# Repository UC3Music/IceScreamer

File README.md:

# IceScreamer
UC3Music's version of the well known green guitar pedal: Ibanez's Tube Screamer.

[Este mismo artículo en español](https://github.com/UC3Music/IceScreamer/blob/master/LEEME.md)

This project has a very similar electronics to Ibanez TS-808 TubeScreamer. Moreover this board let you choose among several modifications of the original design, and implement it easily. The most important modification is the ability to build a true bypass or buffered bypass pedal. Also there will be plenty of room for the most usual mods out there:

- Easier to provide "more gain"
- Easy to replace Op-Amp
- Easy to swap diodes (different distortion sounds)
- Easy to swap between flavors TS5, TS10 and TS808

## Choose from true bypass or pseudo true bypass.
From a manufacture perspective, true bypass isn't a convenient design, since it requires a big and expensive three pole, dual trow switch. And because it's bulkiness and complexity it needs to be soldered by hand. Buffered bypass is the way several manufacturers (Boss, Ibanez) reduced fabrication cost. However you need to solder 30 more components to get buffered bypass working, this circuit is more interesting in very automated manufacturing lines.

Among other benefits, true bypass means that, when your pedal is off, signal passes completely unaltered trough the pedal, as a wire tying together the input and output jack. Your tone will be perfect, however this bypass method has two disadvantages:

- A loud "click" sound can be made at the switch and then amplified by your guitar amp.
- If you are using long cable runs (i.e. 6m from guitar to pedalboard, then 6m from pedalboard to amp) you will have treble loss because guitar's high impedance output signal is affected a lot by cable capacitance.

Pseudo true bypass (buffered bypass) means that, when pedal is off, signal passes trough one or more buffers. A buffer is a kind of amplifier with gain of 1. Neither amplifies or attenuates signal. Buffers are designed to not alter the sound, but according to this [YouTube Video](https://www.youtube.com/watch?v=-oxBlWmeGE0), using more than five buffered pedals, bypass can trim down some bass frequencies and a little high frequencies. The benefits from buffered bypass are:

- No "click" silent switching.
- After the buffered pedal no matter how many cable meters you put, you no longer have treble loss. Pedal's output has low impedance, so cable capacitance reduce highs less.

TL;DR: using a lot of buffered bypass pedals is not good because you can end with a high-passed guitar sound. Using only true bypass pedals is not good if you handle long cable runs. Putting some buffered bypass pedal provide the best of the two worlds solution.

If you choose to build your IceScreamer with true bypass, short only "Short for TruBy" jumper located under "MILK" connector. If you choose to build your IceScreamer with pseudo true bypass, short only the two "Short both for Pseudo" jumpers, located in between input and output jacks.
Do it with a little of solder.

## Let's begin soldering
Components appears in the order it is meant to be soldered, from little to bigger size. If you need advice on how to solder, check this videos.
- [Tutorial SMT4Dummies by David Antón](https://www.youtube.com/watch?v=AYtE7eyIIUI&t=5s) Hand soldering wet technique.
- [Tutorial by informaticaIT](https://www.youtube.com/watch?v=BA7luKtNBzU) SMT with hot air gun.
- [Tutorial by ItsInOurKernel](https://www.youtube.com/watch?v=PU7wLcuqc-I) Hand soldering SMT.
- [Tutorial by EEVBlog](https://youtu.be/b9FC9fAlfQE?t=405) Hand soldering SMT.
- [Tutorial SMT4Dummies de JorFru (Spanish)](https://www.youtube.com/watch?v=6ee5rFPXXJo) Hand soldering dry technique.

## Where to place components?
Check the interactive component placement [viewer](http://music.uc3m.es/IceScreamer/BOM)

### Placing resistors
All resistors are SMD 2012(metric) or SMD 0805(imperial) size. You must have in mind all resistors measure 2,00mm x 1,25mm.
Resistors are thick film metal resistors.
10R stands for 10 ohms, 10K stands for 10000 ohms.

- R1, R2, R5, R6, R10, R15 and R17: 10K
- R3, R9, R11, R13: 1K
- R4, R14: 470K
- R7: 47K
- R8: 4,7K
- R12: 220R
- R16: 100R
- R18: SOLDER ONLY FOR TRUE BYPASS. Current limiting resistor for LED indicator. For using the ring LED provided in the BOM, use 470R. For single red LED on true bypass, use 680R.
- R19: 10K (only in case you are using a linear 100K potentiometer on volume and you want to provide a logarithmic feel)

If you are assembling true bypass, stop here. The following are the resistors for pseudo true bypass.

- R20 and R21: 470K
- R22, R26 and R32: 1M
- R23, R24, R30, R31, R34: 56K
- R25: 22K
- R27: 22R
- R28 and R29: 47K
- R33: 0R
- R35: current limiting resistor for pseudo true bypass LED indicator. 36K for standard red LED. Need calculation for other color.
- R36: 100R

### Capacitors
All capacitors are SMD 2012(metric), 0805(imperial) sized. To clarify: this component measures 2,0mm x 1,25mm.

Ceramic capsin case it is not specified.

- C3, C4, C12, C14, C15, C16, C17 and C18: 100nF
- C5: 22nF.
- C6 y C11: 1uF. Footprints are wrong here, you should solder polyester caps here, for improving the sound.
- C7: 47pF, Trough hole mounted
- C8: 47nF, Trough hole mounted
- C9: 220nF.
- C10: 220nF, Trough hole mounted
- C13: 10uF.

If you are assembling true bypass version, stop here. If you are assembling pseudo true bypass, continue soldering the following caps.
- C20: 100nF
- C21 and C27: 47nF
- C22, C25 and C26: 1nF
- C23 and C24: 100pF

### Diodes
Apart of D1 and D4 which are THD, others are 2012 metric (0805 imperial), however you can solder MicroMELF packages.

- D1: 1N4001, or any other general purpose 1A diode.
- D2 y D3: 1N4148
- D4: LED status (on/off) indicator

If you are assembling true bypass version, stop here. If you are assembling pseudo true bypass, continue soldering the following diodes.

- D20, D21 y D22: 1N4148
- D23: Zener 4.7V

### Transistors
Transistors are placed as seen on paintings on the board. If you are using other than the BC547, wich is suggested, pinouts will differ. Check this picture.

- Q1, Q2: [BC547](https://www.tme.eu/es/details/bc547-cdi/transistores-npn-tht/cdil/bc547/). You can use any NPN transistor, but check pinouts.If you are assembling true bypass version, stop here. If you are assembling pseudo true bypass, continue soldering these transistors.

If you are assembling true bypass version, stop here. If you are assembling pseudo true bypass, continue soldering these transistors.

- Q20, Q21 y Q22: [BC547](https://www.tme.eu/es/details/bc547-cdi/transistores-npn-tht/cdil/bc547/). You can use any NPN transistor, but check pinouts.

- Q23 y Q24: [MMBF4392L](https://www.tme.eu/es/details/mmbf4392lt1g/transistores-con-canal-n-smd/on-semiconductor/). This is a JFET transistor. It's easy to find in CBE configuration.

### Integrated circuit
We recommend to install a socket for easy IC swapping.
U1: JRC4558. We use [RC4558](https://www.tme.eu/es/details/rc4558p/amplificadores-operativos-tht/texas-instruments/), but you can use any "dual OP-Amp", I.E.: NE5532,TL082, etc.

### Potentiometers
- ICE (Drive): 470K lineal
- CREAM (Tone): 20K lineal
- MILK (Level): 100K logarithmic or lineal installing 10K on R19. Learn more about Lin to Log conversion [here](https://learnabout-electronics.org/Resistors/resistors_09a.php)

### Switches
For True Bypass, solder a [3PDT](https://es.aliexpress.com/item/32530834644.html?spm=a2g0s.9042311.0.0.1ec663c0FUsGGv) (also called TPDT) switch in "SW_TruBy" mark.
If you are assembling pseudo true bypass, solder a momentary button [SPST](https://es.aliexpress.com/item/32918205335.html?spm=a2g0o.productlist.0.0.4da0520bgPKH60&algo_pvid=74ea01d2-d432-4e98-9630-f63bd3b4dfa1&algo_expid=74ea01d2-d432-4e98-9630-f63bd3b4dfa1-12&btsid=0b0a01f815821201808298358e4f6b&ws_ab_test=searchweb0_0,searchweb201602_,searchweb201603_) in the "SW_Pseudo" mark. Before soldering, put the cables trough the holes to secure it and avoid damage in case of strong pull.

### Battery cell
Battery cell Connect your battery lead to "9V Batt" mark, mind its polarity. Before soldering, put the cables through the holes to secure it and avoid damage in case of strong pull. Check picture.

### Big components last assembled

- C1 y C2: electrolytic caps, 220-470uF, at least 15V. Better use low-ESR. Lead spacing is 2.54mm.

### Jacks
Input and output are using Amphenol [ACJS-IH](https://www.tme.eu/en/details/acjs-ih/jack-connectors/amphenol/) connectors.
But seems that Neutrik [NMJ6HFD2](https://www.tme.eu/es/details/ntr-nmj6hfd2/conectores-jack/neutrik/nmj6hfd2/) are compatible too, not tested yet.

## Main mods
### More gain
If you want more distortion, lower that 4.7K R8 to get more gain when the drive control is maxed out. If you don't also want to change the bass/treble response, you will need to change the capacitor C8 as well. If you half the resistor, double the capacitor to keep the same overall frequency response. In example, R8 from 4.7K to 2.2K (you can use two 4.7K in parallel), C8 cap from 47nF to 100nF (you can use two 47nF caps in parallel)

It's also possible to increase gain potentiometer's value from 470K to 1M. 

### More bass
Increase C8 value. I.E.: C8 from 47nF to 100nF. Or 200nF if you already done the "more gain" mod.

### Swapping distortion flavour.
The stock units use a pair of silicon signal diodes, which are a 1N4148. If you change one of these diodes, chances are that the resulting pair will not clip at the same voltage for positive and negative signals, giving you asymmetrical clipping, and the resulting even order distortion. If you pick something close, like maybe a silicon power diode like the 1N400x series for the second diode, the resulting second harmonic will be very subtle, not audible as an octave effect at all, just a "sweeter" or more liquid tone.

You can try a number of things like putting one germanium (1N34A from Radio Shack works) diode in series with one of the silicons to add a bit more threshold voltage to one side. A more radical treatment would be the replacement of one of the silicons with three germaniums; even more radical would replace one of the silicons with TWO silicons. These last will start to make an octave effect just barely audible at some notes on the guitar neck.

I've even heard of using LED's in there for the clipping diodes. Go wild here.

## Otros mods:
On [this site](https://www.electrosmash.com/tube-screamer-analysis) I read that [this transistors](https://www.tme.eu/es/details/2sc1815-cen/transistores-npn-tht/central-semiconductor-corp/2sc1815/) are more silent than the suggested BC547. But check pin out when swapping transistors! However, on first prototypes, there's no noise issues with suggested parts. Through Q1 and Q2 is sound passing by, meanwhile there's no signal passing through Q20, Q21 nor Q22. If you are interesting in transistor swapping, consider only doing it on Q1 and Q2.

## References
This project and documentation were inspired in the following posts:
- http://www.geofex.com/Article_Folders/TStech/tsxfram.htm
- https://www.electrosmash.com/tube-screamer-analysis
- https://www.muzique.com/tech/scream.htm

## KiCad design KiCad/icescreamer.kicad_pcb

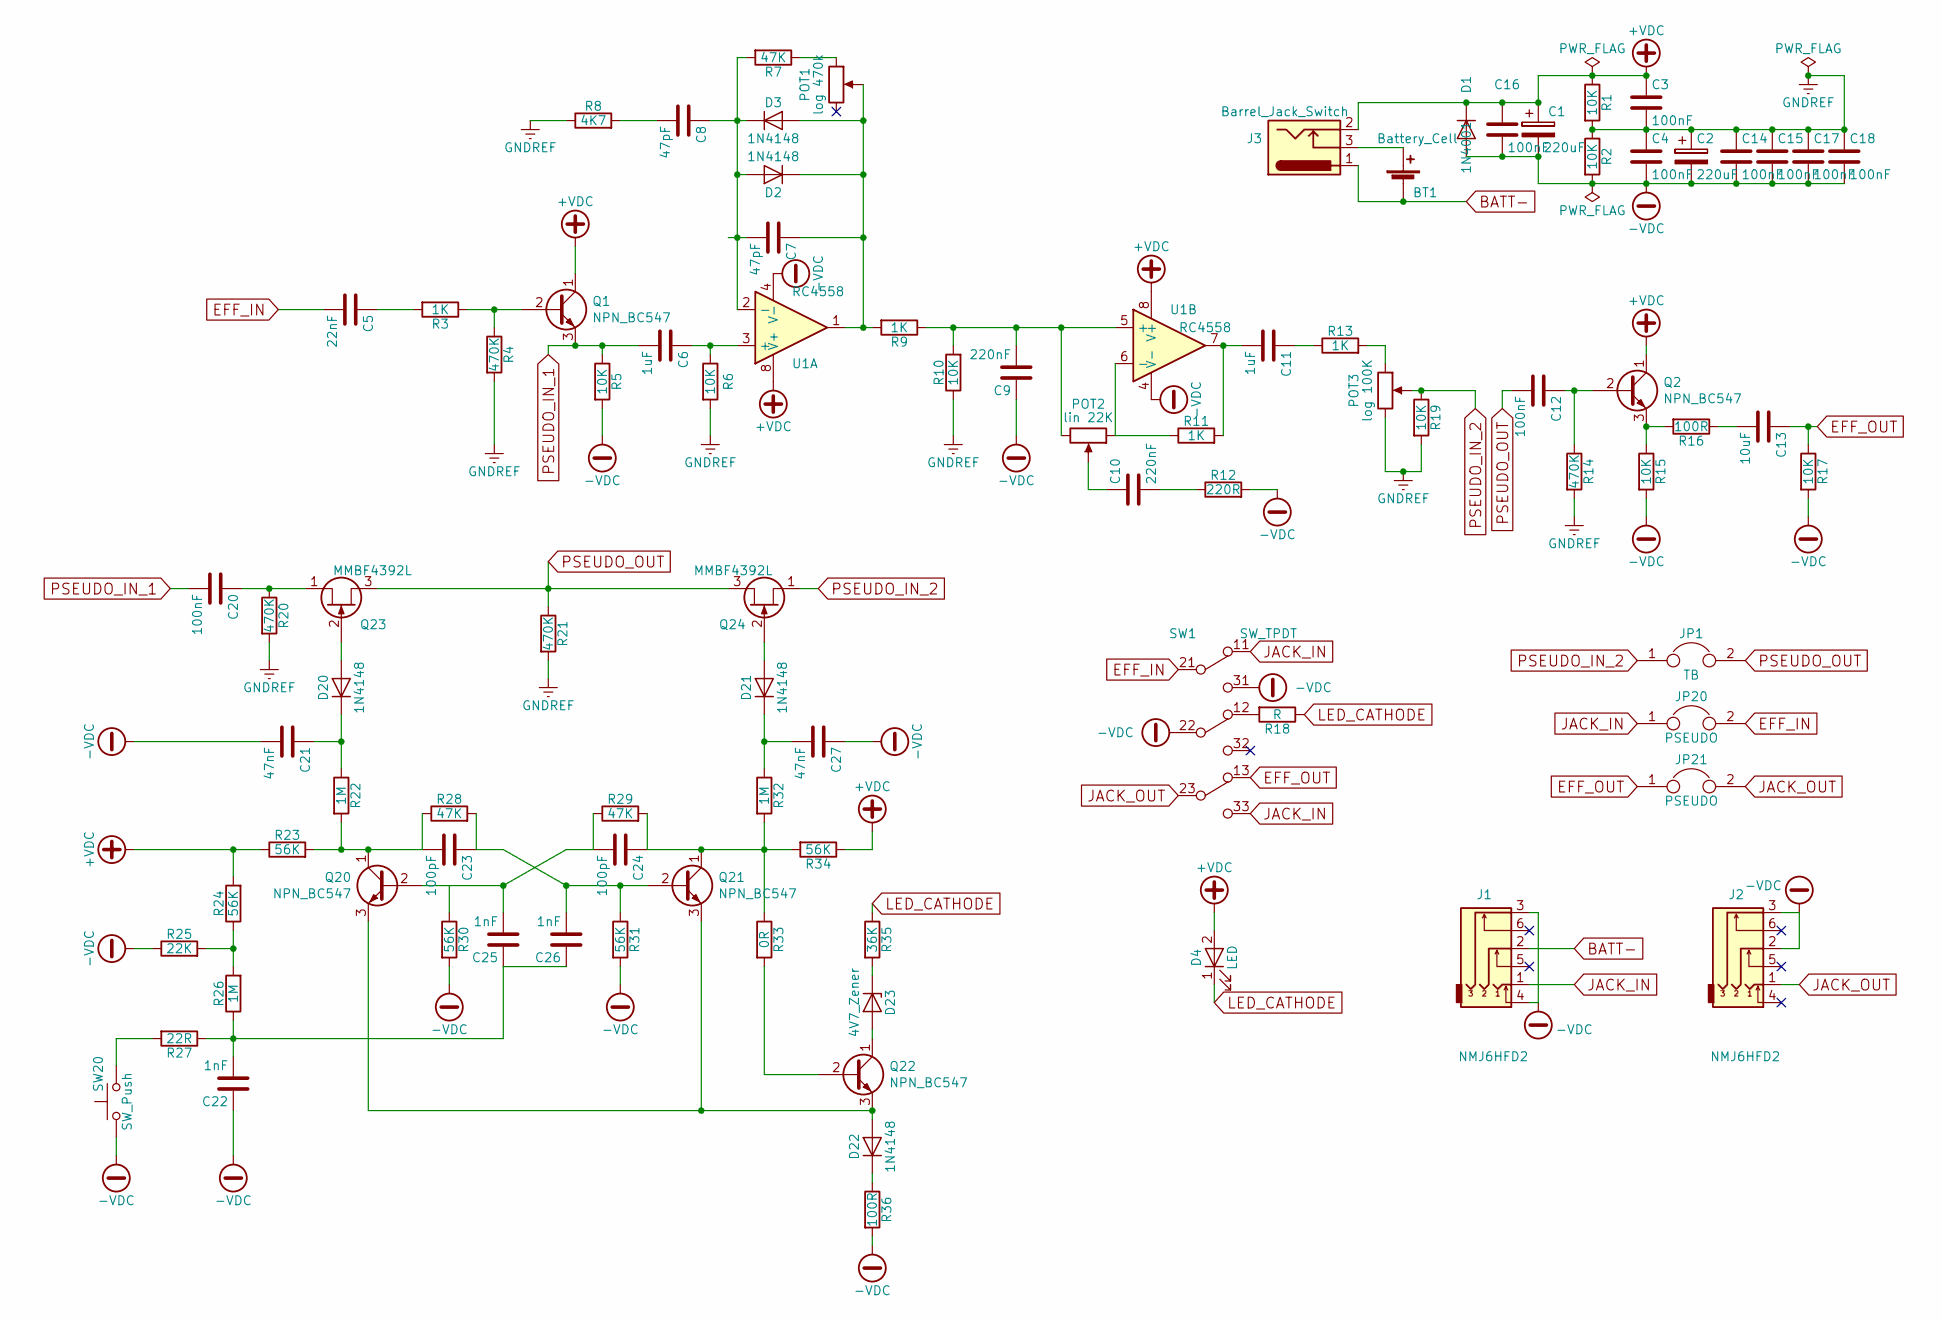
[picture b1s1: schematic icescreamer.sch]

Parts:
BT1: Battery_Cell; 1x02_P2.54mm_Hole
C1, C2: 220uF; CP_Radial_D6.3mm_P2.50mm
C3, C4, C12, C14, C15, C16, C17, C18, C20: 100nF; C_0805_2012Metric_Pad1.15x1.40mm_HandSolder
C5: 22nF; C_0805_2012Metric_Pad1.15x1.40mm_HandSolder
C6, C11: 1uF; C_0805_2012Metric_Pad1.15x1.40mm_HandSolder
C7, C8: 47pF; C_Rect_L7.0mm_W3.5mm_P2.50mm_P5.00mm
C9: 220nF; C_0805_2012Metric_Pad1.15x1.40mm_HandSolder
C10: 220nF; C_Rect_L7.0mm_W3.5mm_P2.50mm_P5.00mm
C13: 10uF; C_0805_2012Metric_Pad1.15x1.40mm_HandSolder
C21, C27: 47nF; C_0805_2012Metric_Pad1.15x1.40mm_HandSolder
C22, C25, C26: 1nF; C_0805_2012Metric_Pad1.15x1.40mm_HandSolder
C23, C24: 100pF; C_0805_2012Metric_Pad1.15x1.40mm_HandSolder
D1: 1N4001; D_DO-41_SOD81_P7.62mm_Horizontal
D2, D3: 1N4148; D_MELF-RM10_Universal_Handsoldering
D4: LED; PinHeader_1x02_P2.00mm_Vertical
D20, D21, D22: 1N4148; D_0805_2012Metric_Pad1.15x1.40mm_HandSolder
D23: 4V7_Zener; D_MiniMELF_Handsoldering
J1, J2: NMJ6HFD2; IceJACK
J3: Barrel_Jack_Switch; PinHeader_1x03_P2.54mm_Vertical
JP1: TB; SolderJumper-2_P1.3mm_Open_RoundedPad1.0x1.5mm
JP20, JP21: PSEUDO; SolderJumper-2_P1.3mm_Open_RoundedPad1.0x1.5mm
POT1: log 470k; PinHeader_1x03_P2.54mm_Vertical
POT2: lin 22K; PinHeader_1x03_P2.54mm_Vertical
POT3: log 100K; PinHeader_1x03_P2.54mm_Vertical
Q1, Q2, Q20, Q21, Q22: NPN_BC547; TO-92_SOT23_JorFru_compact
Q23, Q24: MMBF4392L; TO-92_SOT23_JorFru_compact
R1, R2, R5, R6, R10, R15, R17, R19: 10K; R_0805_2012Metric_Pad1.15x1.40mm_HandSolder
R3, R9, R11, R13: 1K; R_0805_2012Metric_Pad1.15x1.40mm_HandSolder
R4, R14, R20, R21: 470K; R_0805_2012Metric_Pad1.15x1.40mm_HandSolder
R7, R28, R29: 47K; R_0805_2012Metric_Pad1.15x1.40mm_HandSolder
R8: 4K7; R_0805_2012Metric_Pad1.15x1.40mm_HandSolder
R12: 220R; R_0805_2012Metric_Pad1.15x1.40mm_HandSolder
R16, R36: 100R; R_0805_2012Metric_Pad1.15x1.40mm_HandSolder
R18: R; R_0805_2012Metric_Pad1.15x1.40mm_HandSolder
R22, R26, R32: 1M; R_0805_2012Metric_Pad1.15x1.40mm_HandSolder
R23, R24, R30, R31, R34: 56K; R_0805_2012Metric_Pad1.15x1.40mm_HandSolder
R25: 22K; R_0805_2012Metric_Pad1.15x1.40mm_HandSolder
R27: 22R; R_0805_2012Metric_Pad1.15x1.40mm_HandSolder
R33: 0R; R_0805_2012Metric_Pad1.15x1.40mm_HandSolder
R35: 36K; R_0805_2012Metric_Pad1.15x1.40mm_HandSolder
SW1: SW_TPDT; IceStomp_Switch_3PDT
SW20: SW_Push; 1x02_P2.54mm_Hole
U1: RC4558; DIP8+SOIC8_2

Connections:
+VDC: C1.1, C3.1, C16.1, D1.1 (K), D4.2 (A), J3.2, Q1.1 (C), Q2.1 (C), R1.1, R23.1, R24.2, R34.1, U1.8 (V+)
-VDC: C1.2, C2.2, C4.2, C9.1, C14.2, C15.2, C16.2, C17.2, C18.2, C21.2, C22.1, C27.1, D1.2 (A), J1.3, J1.4, J2.2, J2.3, R2.2, R5.2, R12.2, R15.2, R17.2, R25.1, R30.2, R31.2, R36.2, SW1.22, SW1.31, SW20.1, U1.4 (V-)
BATT-: BT1.2 (-), J1.2, J3.1
EFF_IN: C5.2, JP20.2, SW1.21
EFF_OUT: C13.1, JP21.1, R17.1, SW1.13
GNDREF: C2.1, C3.2, C4.1, C14.1, C15.1, C17.1, C18.1, POT3.3, R1.2, R2.1, R4.2, R6.2, R8.1, R10.1, R14.2, R19.2, R20.2, R21.2
JACK_IN: J1.1, JP20.1, SW1.11, SW1.33
JACK_OUT: J2.1, JP21.2, SW1.23
LED_CATHODE: D4.1 (K), R18.1, R35.1
unnamed: BT1.1 (+), J3.3
unnamed: C5.1, R3.2
unnamed: C6.1, R6.1, U1.3 (+)
unnamed: C7.1, D2.1 (K), D3.2 (A), POT1.2, R9.2, U1.1
unnamed: C7.2, C8.1, D2.2 (A), D3.1 (K), R7.2, U1.2 (-)
unnamed: C8.2, R8.2
unnamed: C9.2, POT2.3, R9.1, R10.2, U1.5 (+)
unnamed: C10.1, POT2.2
unnamed: C10.2, R12.1
unnamed: C11.1, R13.1
unnamed: C11.2, R11.2, U1.7
unnamed: C12.1, Q2.2 (B), R14.1
unnamed: C13.2, R16.1
unnamed: C20.1, Q23.1 (S), R20.1
unnamed: C21.1, D20.1 (K), R22.1
unnamed: C22.2, C25.1, C26.1, R26.1, R27.1
unnamed: C23.1, C26.2, Q21.2 (B), R28.2, R31.1
unnamed: C23.2, Q20.1 (C), R22.2, R23.2, R28.1
unnamed: C24.1, Q21.1 (C), R29.2, R32.2, R33.1, R34.2
unnamed: C24.2, C25.2, Q20.2 (B), R29.1, R30.1
unnamed: C27.2, D21.1 (K), R32.1
unnamed: D20.2 (A), Q23.2 (G)
unnamed: D21.2 (A), Q24.2 (G)
unnamed: D22.1 (K), R36.1
unnamed: D22.2 (A), Q20.3 (E), Q21.3 (E), Q22.3 (E)
unnamed: D23.1 (K), R35.2
unnamed: D23.2 (A), Q22.1 (C)
unnamed: POT1.1, R7.1
unnamed: POT2.1, R11.1, U1.6 (-)
unnamed: POT3.1, R13.2
unnamed: Q1.2 (B), R3.1, R4.1
unnamed: Q2.3 (E), R15.1, R16.2
unnamed: Q22.2 (B), R33.2
unnamed: R18.2, SW1.12
unnamed: R24.1, R25.2, R26.2
unnamed: R27.2, SW20.2
PSEUDO_IN_1: C6.2, C20.2, Q1.3 (E), R5.1
PSEUDO_IN_2: JP1.1, POT3.2, Q24.1 (S), R19.1
PSEUDO_OUT: C12.2, JP1.2, Q23.3 (D), Q24.3 (D), R21.1

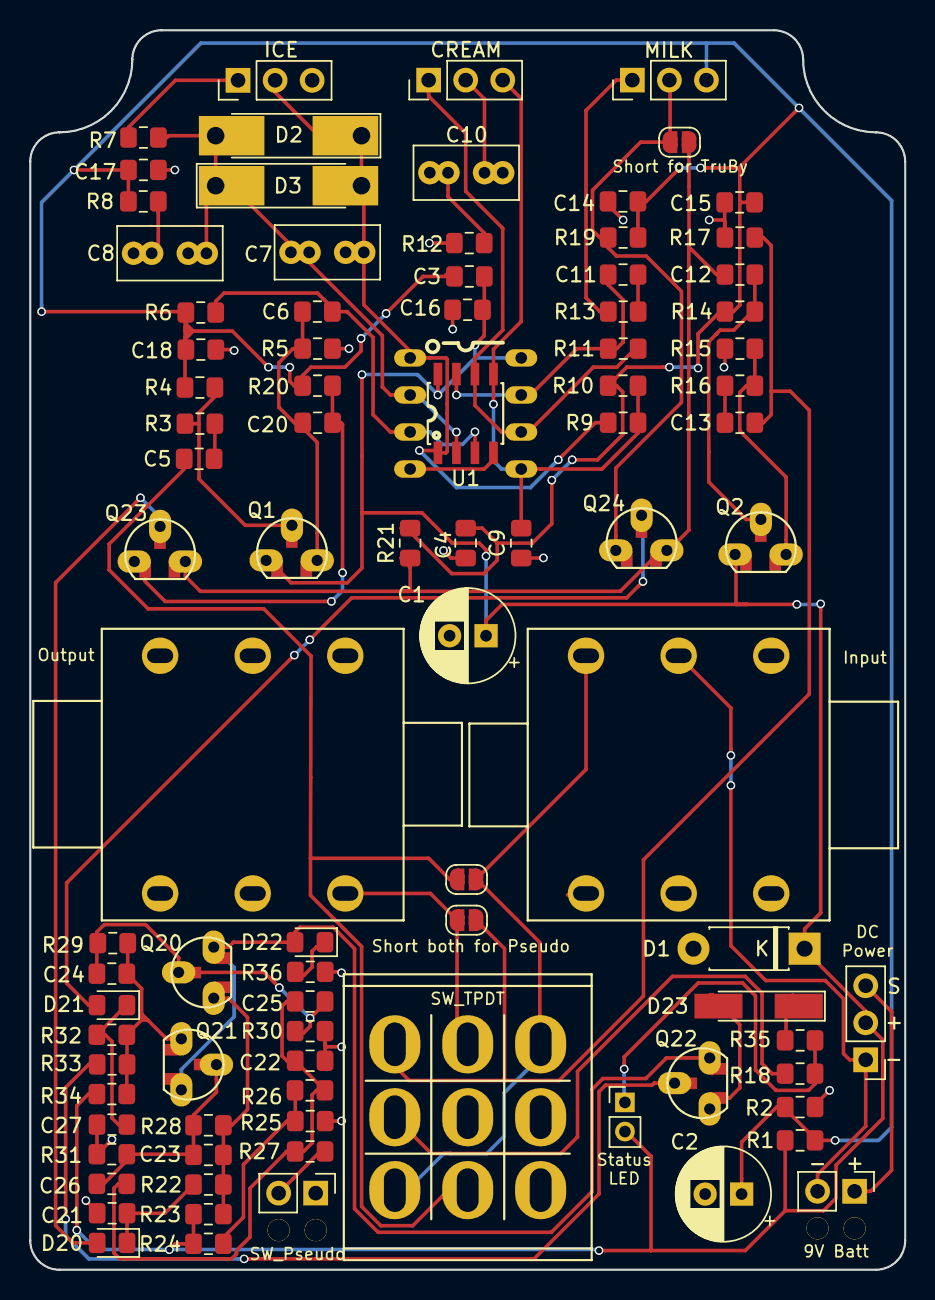
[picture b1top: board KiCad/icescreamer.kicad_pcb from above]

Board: 2 copper layers, 60.0 x 85.0 mm, 90 parts (0 on the bottom side), 48 nets.

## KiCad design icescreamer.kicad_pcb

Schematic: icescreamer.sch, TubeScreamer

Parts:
C1: 0.02uF
C2, C9, C10, C14: 1uF
C3: 0.047uF
C4: 51pF
C5, C6: 0.22uF
C7: 220uF
C8, C12, C13: 0.1uF
C11: 0.1Uf
CON1: BARREL_JACK
D1, D2, D4: DIODE
D3: LED
J1, J2: JACK
P1: CONN_2
Q1, Q2: NPN
R1, R7, R10, R12: 1K
R2, R13: 510K
R3, R4, R8, R14, R16: 10K
R5: 4.7K
R6: 51K
R9: 220R
R11: 4K7
R15: 100R
R17: 20K
RV1: 500KA
RV2: 20K
RV3: 100KA
SW1: 3PDT
U1: TL072
U2: TLE2426NR

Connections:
+5V: C7.1, C8.1, C12.1, CON1.2, D3.1 (A), D4.2 (K), Q1.3 (C), Q2.3 (C), U1.8 (V+), U2.1 (IN)
-5V: C5.2, C7.2, C8.2, C10.2, C13.2, D4.1 (A), J1.S, J1.TS, J2.S, R3.2, R5.2, R9.2, R14.2, R16.2, SW1.6, U1.4 (V-), U2.2 (COMMON)
FX in: C1.2, SW1.2
FX out: C14.2, R16.1, SW1.4
GND: C12.2, C13.1, R2.2, R4.2, R8.1, R13.2, R17.2, RV1.SHLD, RV2.SHLD, RV3.3, RV3.SHLD, U2.3 (OUT)
unnamed: R11.2, SW1.3
unnamed: D3.2 (K), R11.1
unnamed: CON1.3, P1.1
unnamed: R12.1, RV3.1
unnamed: J2.T, SW1.1, SW1.8
unnamed: J1.T, SW1.5
unnamed: C6.1, RV2.2
unnamed: C9.2, R10.2, U1.7
unnamed: C6.2, R9.1
unnamed: R10.1, RV2.1, U1.6 (-)
unnamed: C5.1, R7.2, R8.2, RV2.3, U1.5 (+)
unnamed: C14.1, R15.2
unnamed: Q2.1 (E), R14.1, R15.1
unnamed: C11.2, Q2.2 (B), R13.1
unnamed: C9.1, R12.2
unnamed: CON1.1, J1.R, P1.2 (PM)
unnamed: C10.1, U2.8
unnamed: C11.1, R17.1, RV3.2
unnamed: C3.2, R5.1
unnamed: C2.1, Q1.1 (E), R3.1
unnamed: C1.1, R1.1
unnamed: R6.2, RV1.1
unnamed: Q1.2 (B), R1.2, R2.1
unnamed: C4.2, D1.2 (K), D2.1 (A), R7.1, RV1.2, U1.1
unnamed: C3.1, C4.1, D1.1 (A), D2.2 (K), R6.1, U1.2 (-)
unnamed: C2.2, R4.1, U1.3 (+)

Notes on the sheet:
Recommended transistors: (low noise) MPSA18 2N5089
Optional: to convert linear pot to log pot
INPUT
OUTPUT JACK
POWER INPUT

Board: 2 copper layers, 47 parts (0 on the bottom side), 31 nets, no tracks yet.

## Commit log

2015-03-24 Added kicad-library as submodule
2015-03-24 Add gitignore
2015-03-24 Add schematic files
2015-03-24 Add readme
2015-03-24 Add some values
2015-03-30 colocados los valores de los componentes
2015-03-30 renamed files
2015-03-30 schematic almost finished
2015-03-30 eeeeinnnn?
2015-03-31 after some night-working!
2015-04-05 Correct issues in schematic, add pcb file
2015-04-05 Add outline
2015-04-05 Add components to pcb file, add temp component to this main repo as backup
2015-04-06 Add comment about recommended transistors
2015-04-07 Add resistor to convert volume pot from linear to log
2015-04-07 Updated kicad-lib with female jack symbol
2015-04-07 Update jack symbol in schematic
2015-04-07 Update footprint for female jack in netlist
2015-04-12 Changed submodule from using ssh to using https (does not require a ssh key)
2015-04-12 added pot footprint
2015-04-12 added pots
2015-04-12 borrado el antiguo
2015-04-18 Update female jack pinout
2015-05-03 Added TPDT footswith
2015-05-03 Add new footprints
2015-07-26 Add CAD files for pedal
2016-11-10 Added docs to doc folder and moved KiCad files to folder KiCad
2017-02-19 La mascota del pedal (?)
2017-07-17 Added BOM
2017-07-18 Updated components on schematic with newer ones. EdgeCuts on board already has the proper size. Added custom potentiometer footprint.
2017-08-29 added IceJACK footprint and adjusted edge cuts
2017-08-29 new edge cuts. It should work
2017-12-12 REDOed Schematic. Now supports both TrueBypass and PseudoBypass at the same time
2017-12-13 Asociadas las huellas a los componentes
    Falta trabajar sobre esto, cotejando los componentes que se compraron y comprobar que las huellas que se eligen sean adecuadas para soldar a mano.
2017-12-14 Updated asociación de huellas
2017-12-15 Lo mismo que antes pero un poco más afinado.
2017-12-17 Añadidos archivos de huellas
    DIP8+SOIC8 importado de Drawdio
    3PDT tomado de def-footprints
2017-12-20 Colocando componentes
2017-12-21 Colocando componentes II
2018-02-02 pseudo circuit laid out
2020-01-30 JorFru approved
2020-02-02 V0.3 ready
2020-02-03 V0.3 release
2020-02-04 arreglado problema con el dibujo trasero
2020-02-09 mandado a fabricar, ya no hay vuelta atrás
2020-02-17 Mejoras integrales
2020-02-19 Añadido BOM condensadores
2020-02-19 Añadidas resistencias
2020-02-19 Añadidos diodos
2020-02-19 Añadidos mods
2020-02-19 actualizada información de los condensadores
2020-03-17 añadidas fotos
2020-03-17 añadida foto
2020-03-18 Traducción
2020-03-29 añadido BOM interactivo
2020-03-31 update de la PCB con los valores de los componentes marcados
2020-03-31 añadido BOM actualizado
2020-03-31 fotos añadidas, docs borrados
2020-03-31 renombrada carpeta CAD, archivos antiguos que ya no se usan
2020-03-31 añadida la fuente de las letras
2020-04-04 Intentando ver bom como web
2020-04-04 Rename index.html to BOM.html
2020-04-15 archivos viejos archivados
